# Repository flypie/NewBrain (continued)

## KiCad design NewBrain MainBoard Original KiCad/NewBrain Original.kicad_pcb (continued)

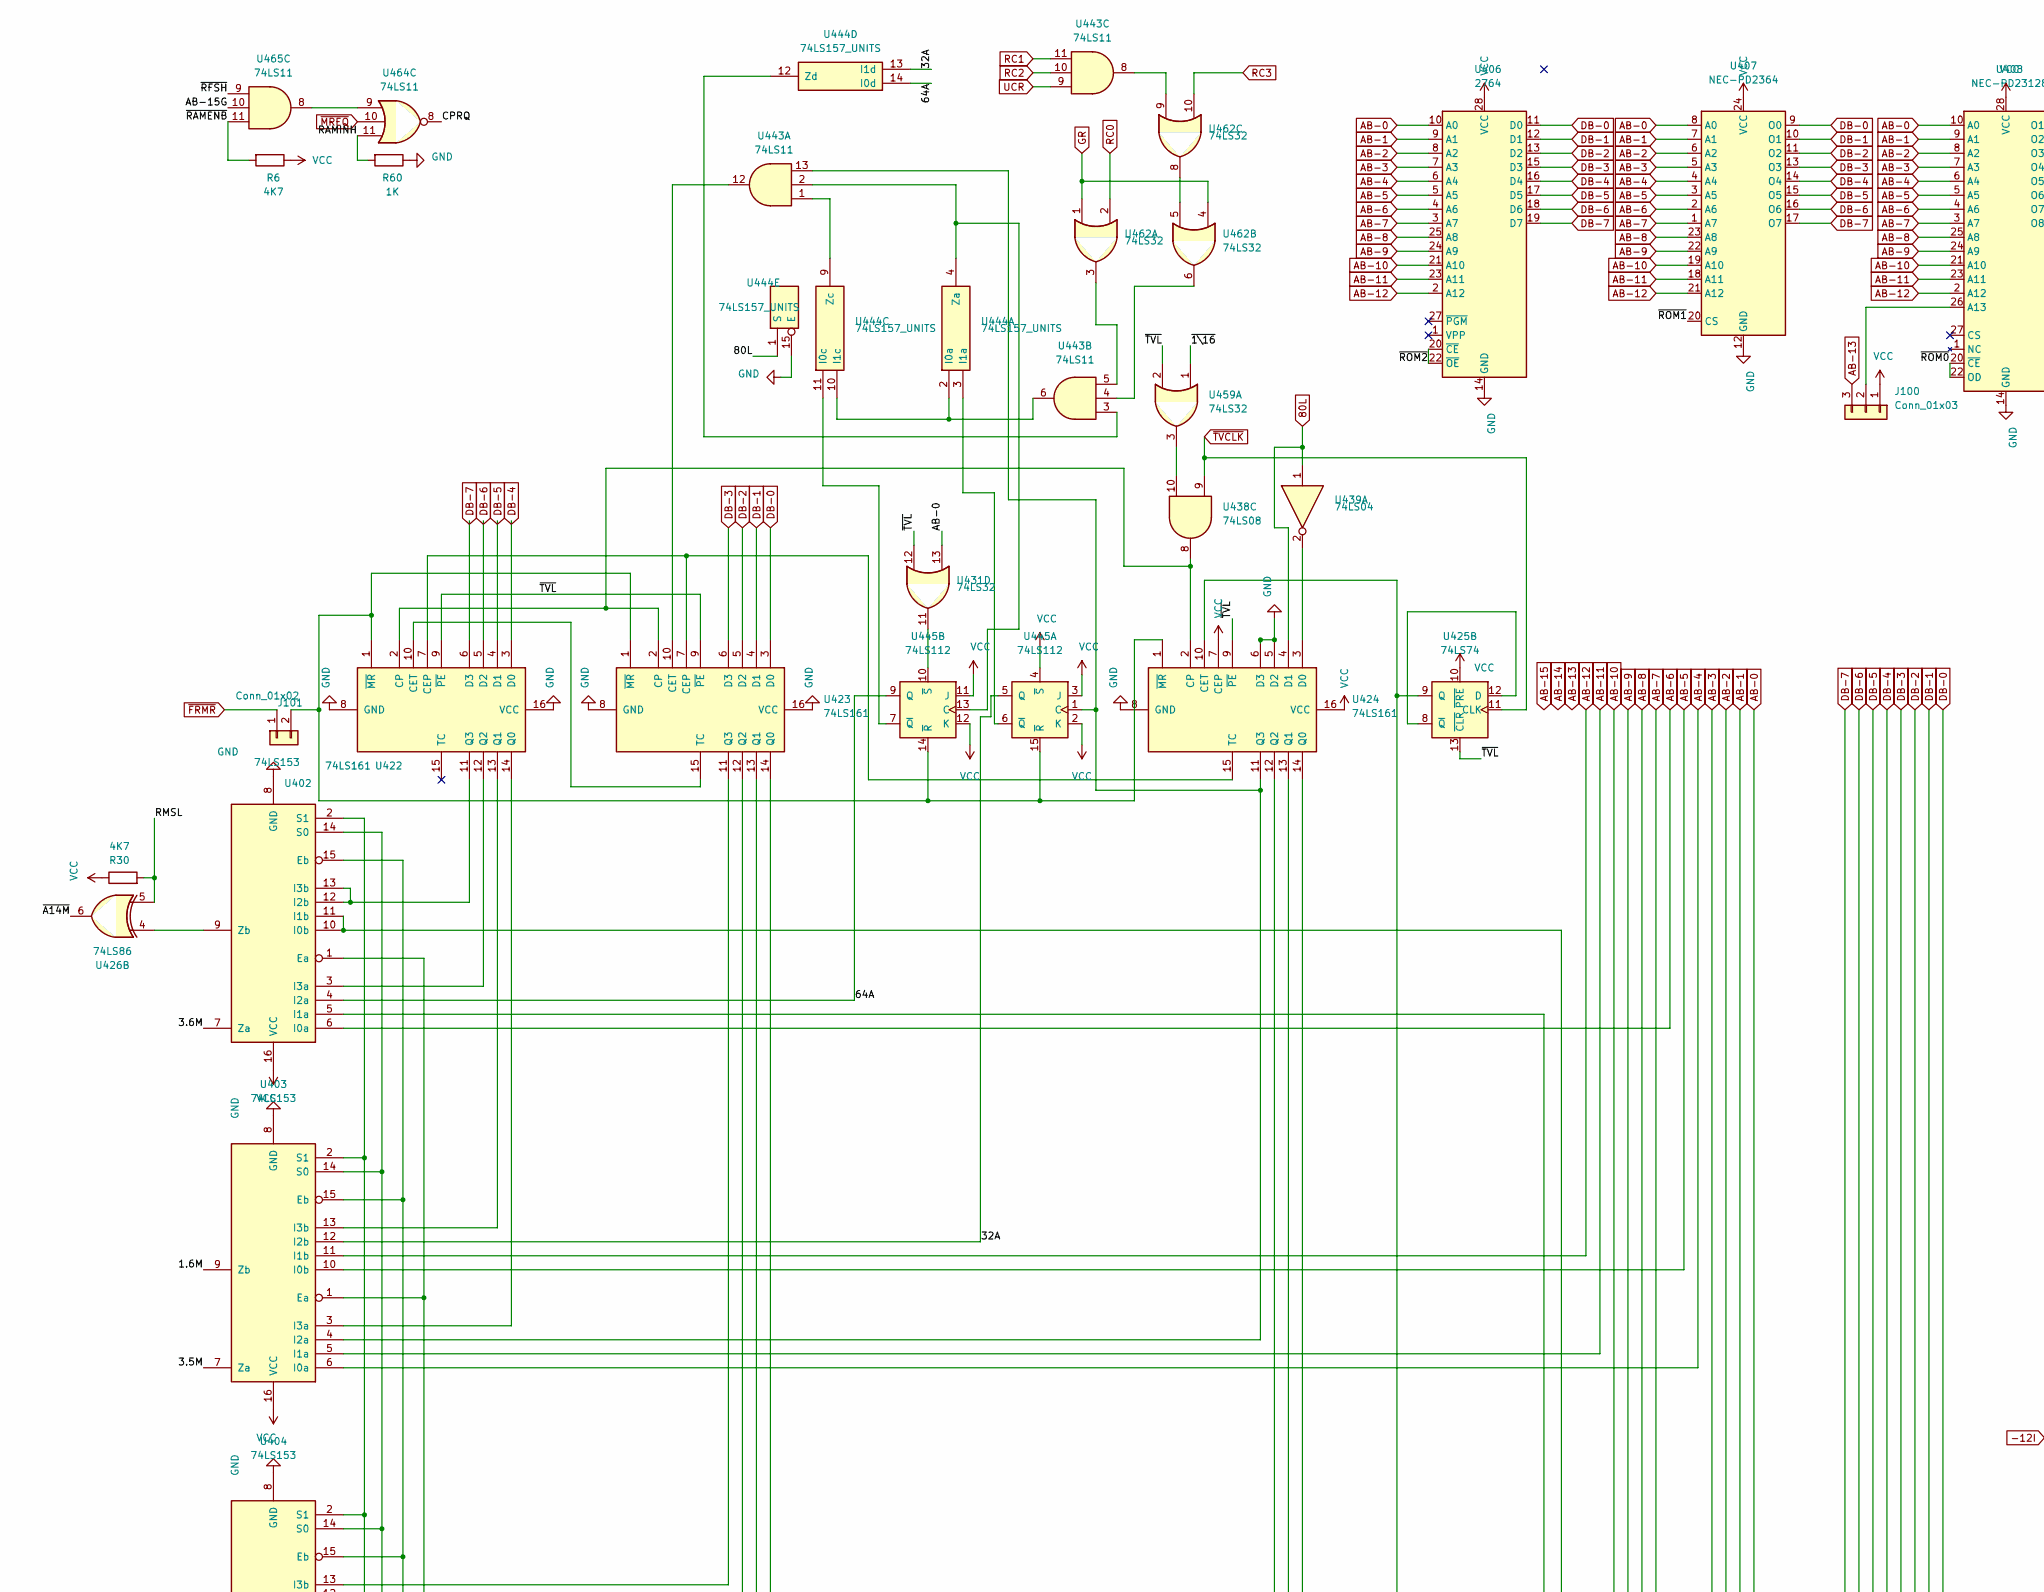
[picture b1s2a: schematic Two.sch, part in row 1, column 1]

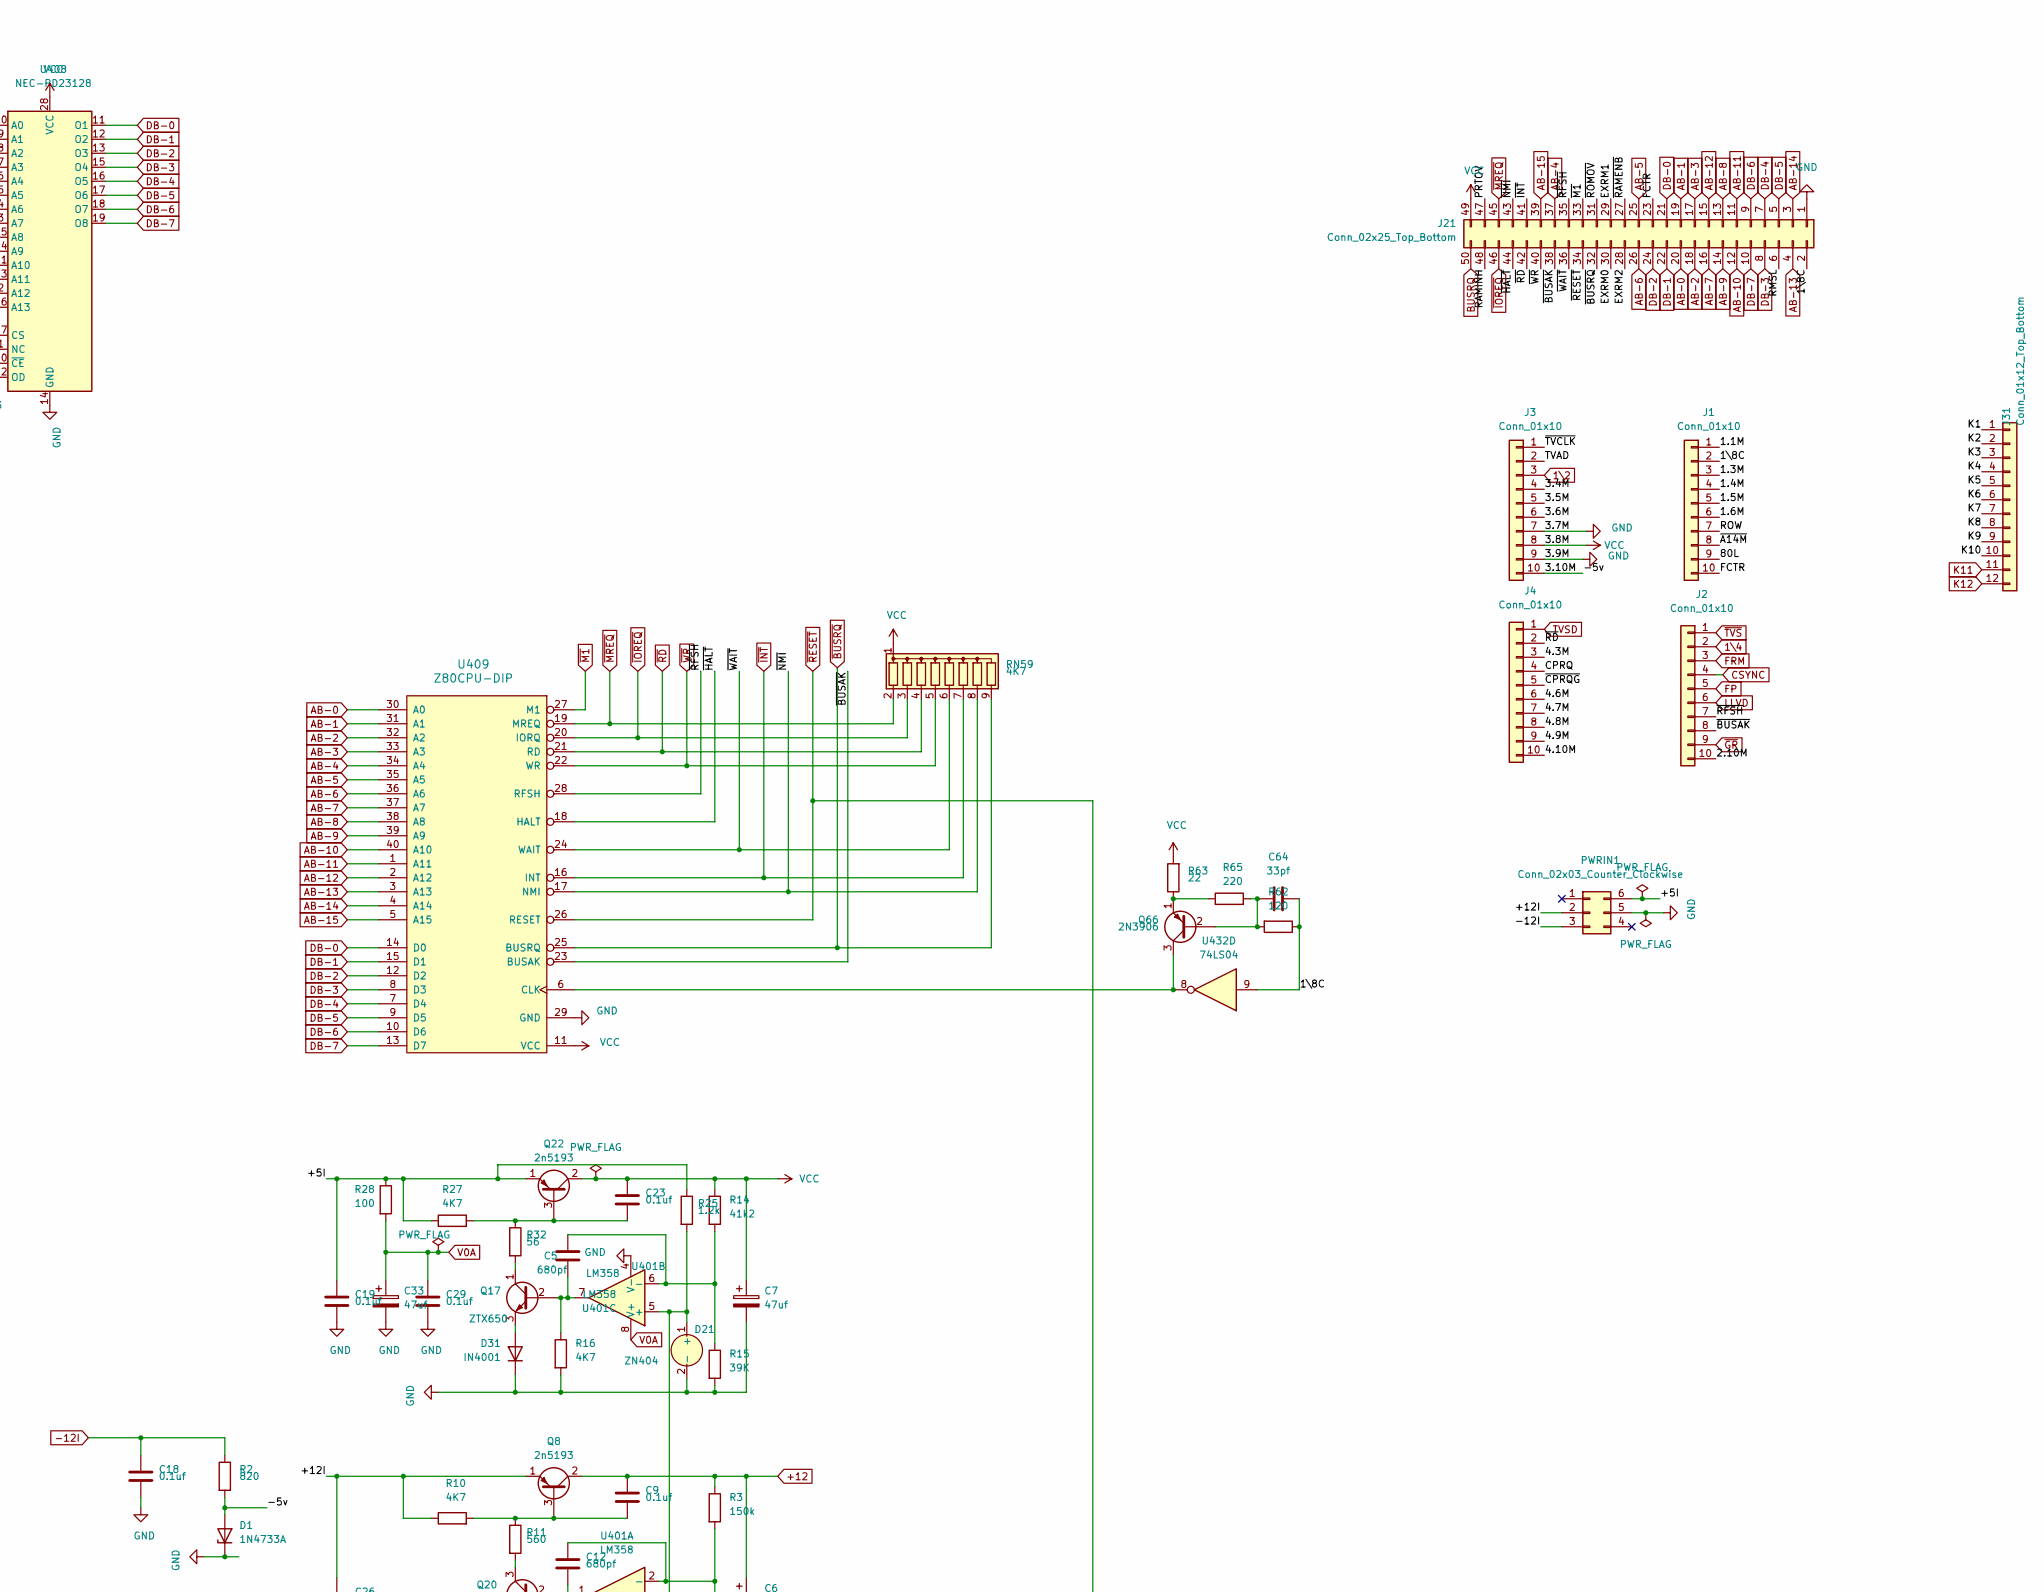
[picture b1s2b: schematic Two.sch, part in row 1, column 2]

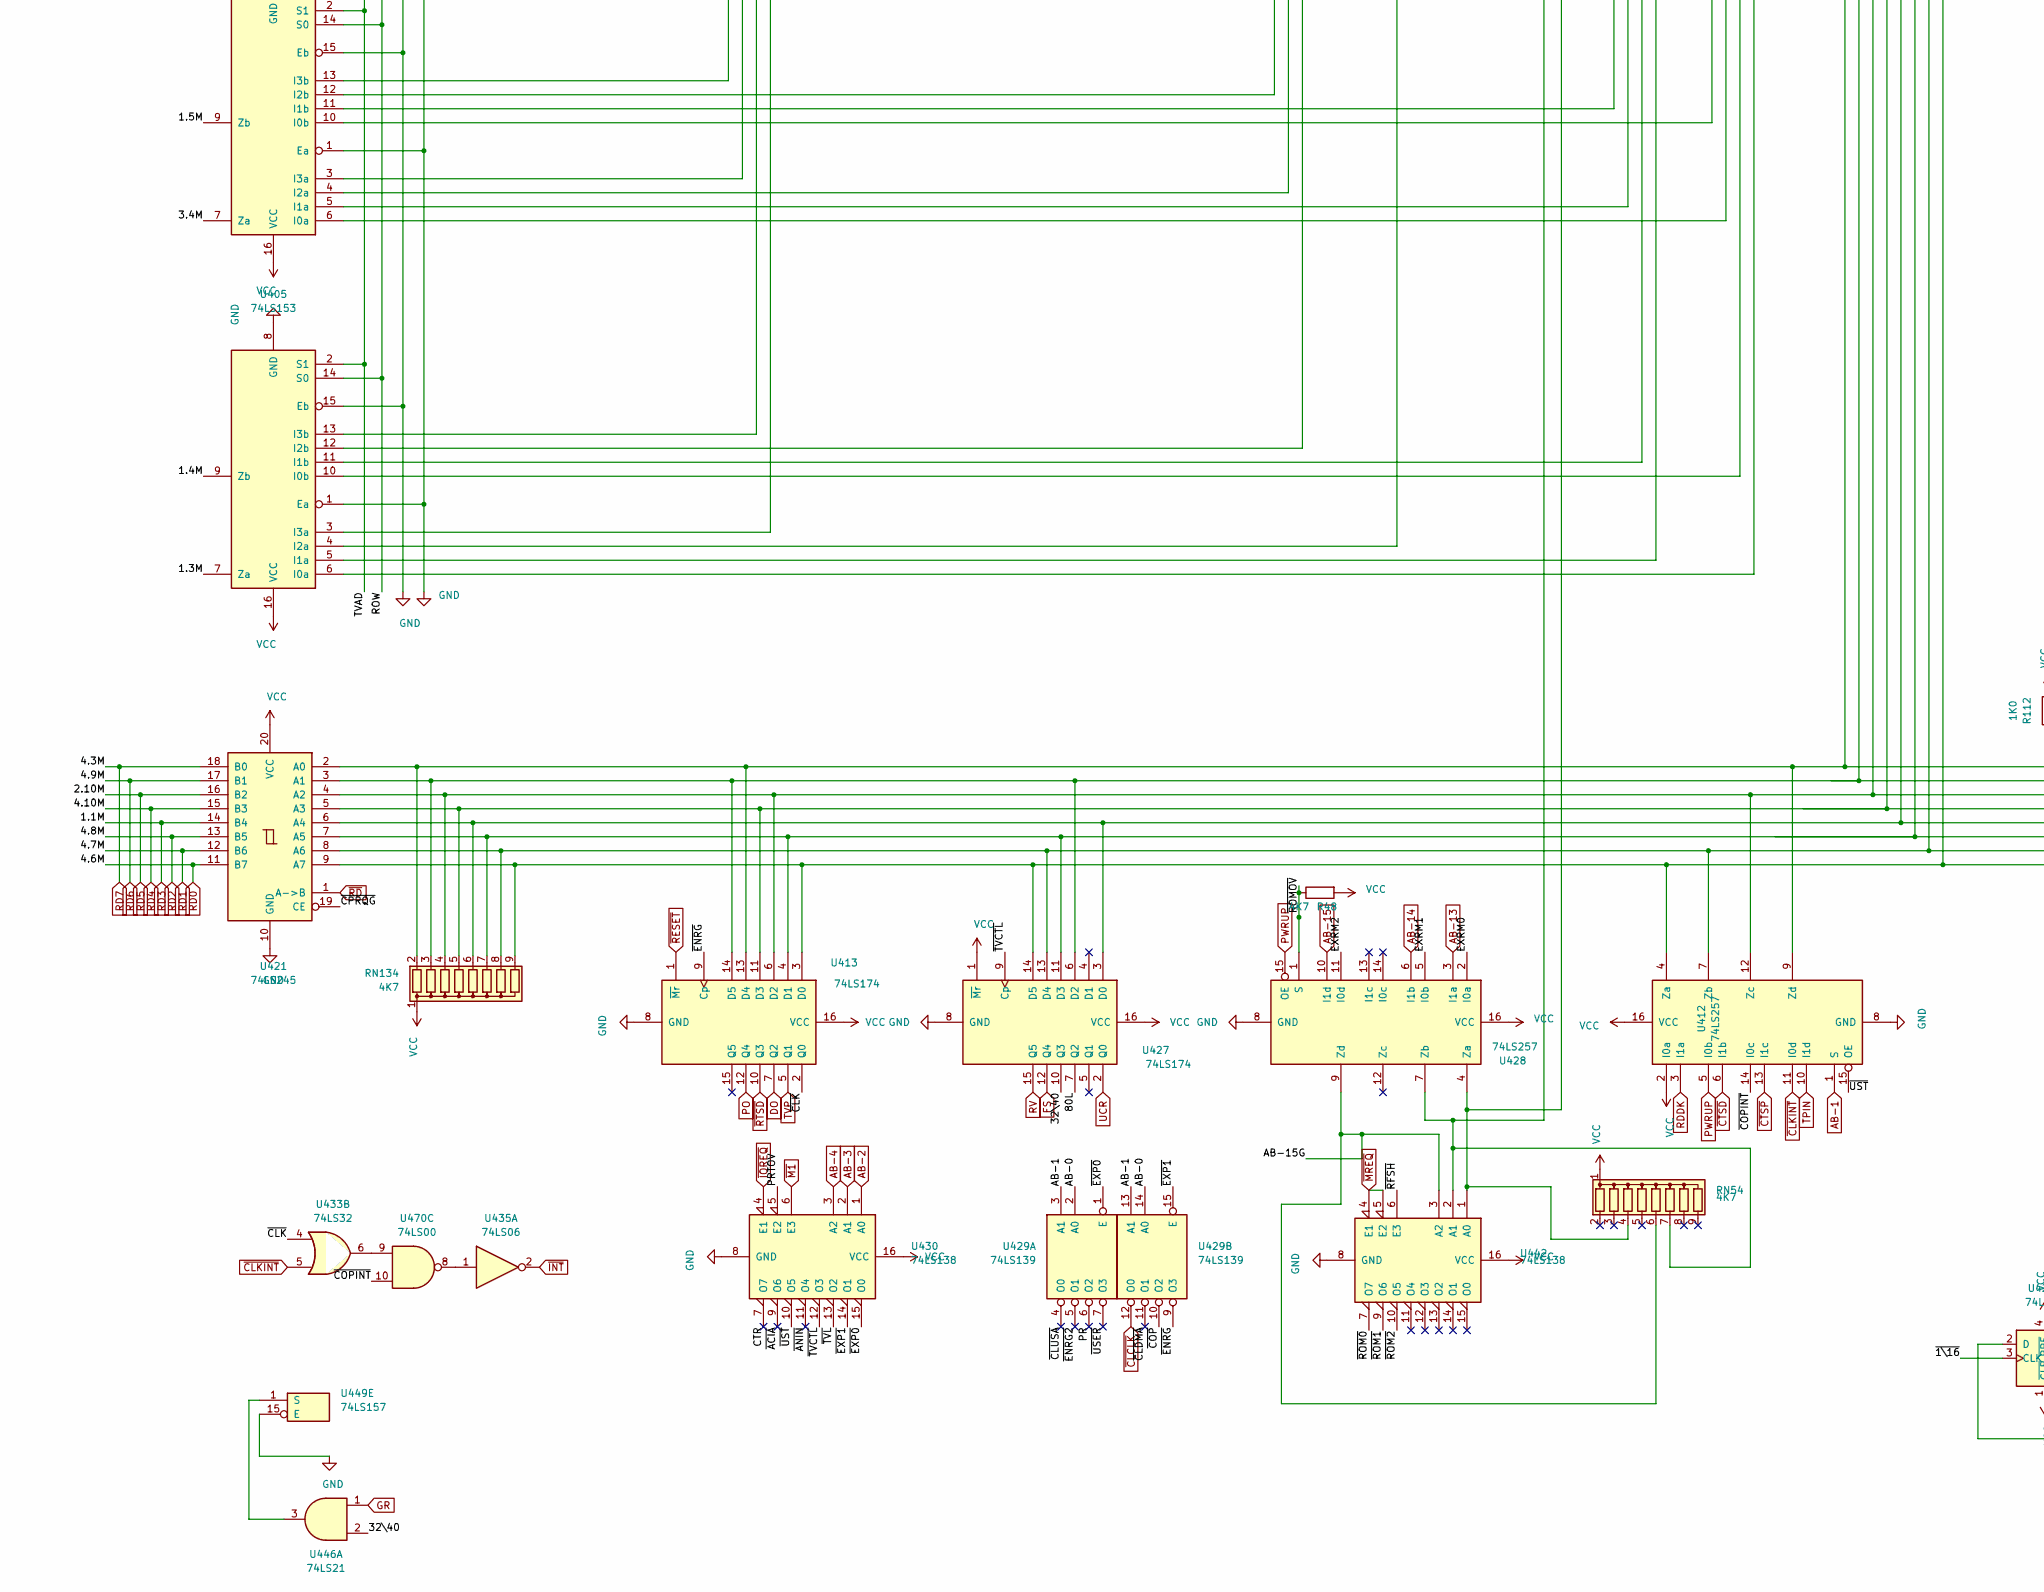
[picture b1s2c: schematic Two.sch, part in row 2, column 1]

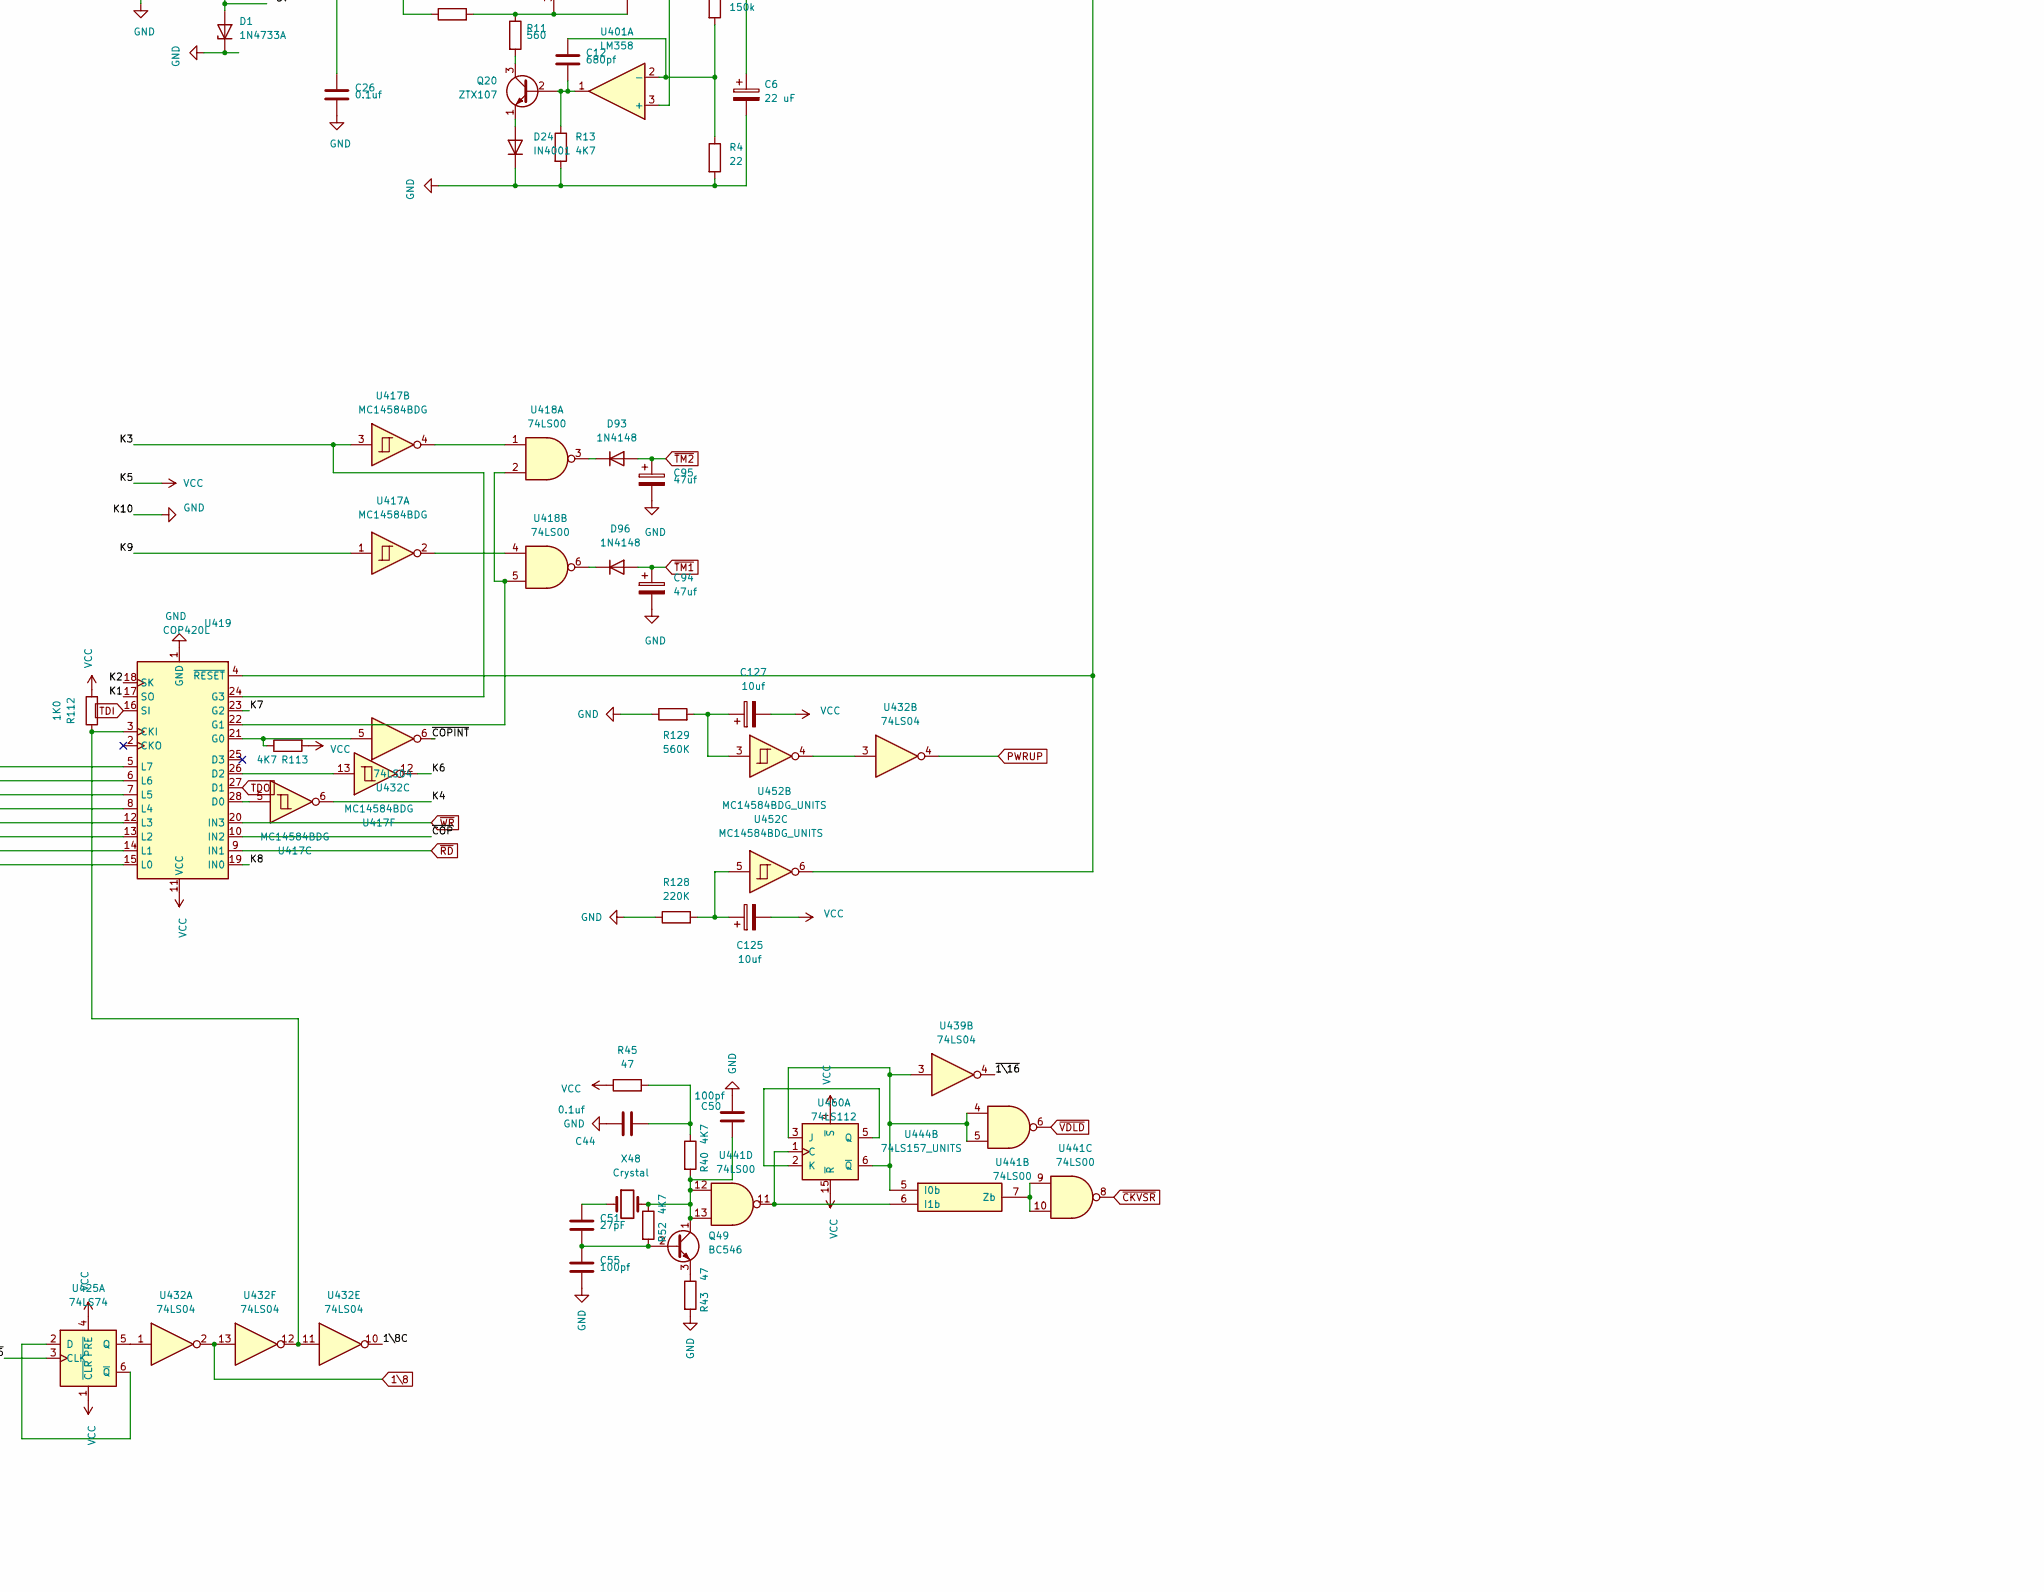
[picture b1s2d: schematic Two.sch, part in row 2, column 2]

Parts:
C5, C12: 680pf; C_Disc_D3.0mm_W1.6mm_P2.50mm
C6: 22 uF; CP_Radial_D4.0mm_P1.50mm
C7, C33, C94, C95: 47uf; CP_Radial_D4.0mm_P1.50mm
C9, C18, C19, C23, C26, C29, C44: 0.1uf; C_Disc_D3.0mm_W1.6mm_P2.50mm
C50, C55: 100pf; C_Disc_D3.0mm_W1.6mm_P2.50mm
C51: 27pF; C_Disc_D3.0mm_W1.6mm_P2.50mm
C64: 33pf; C_Disc_D3.0mm_W1.6mm_P2.50mm
C125, C127: 10uf; CP_Radial_D4.0mm_P1.50mm
D1: 1N4733A; D_DO-34_SOD68_P2.54mm_Vertical_AnodeUp
D21: ZN404; TO-18-2
D24, D31: IN4001; D_DO-34_SOD68_P2.54mm_Vertical_AnodeUp
D93, D96: 1N4148; D_DO-34_SOD68_P2.54mm_Vertical_AnodeUp
J1, J2, J3, J4: Conn_01x10; JST_EH_B10B-EH-A_1x10_P2.50mm_Vertical
J21: Conn_02x25_Top_Bottom; PinHeader_2x25_P2.54mm_Vertical
J31: Conn_01x12_Top_Bottom; JST_EH_B12B-EH-A_1x12_P2.50mm_Vertical
J100: Conn_01x03; PinSocket_1x03_P2.54mm_Vertical
J101: Conn_01x02; PinSocket_1x02_P2.54mm_Vertical
PWRIN1: Conn_02x03_Counter_Clockwise; PinHeader_2x03_P2.54mm_Vertical
Q8, Q22: 2n5193; TO-126-3_Vertical
Q17: ZTX650; TO-92_Inline
Q20: ZTX107; TO-92_Inline
Q49: BC546; TO-92_Inline
Q66: 2N3906; TO-92_Inline
R2: 820; R_Axial_DIN0204_L3.6mm_D1.6mm_P1.90mm_Vertical
R3: 150k; R_Axial_DIN0204_L3.6mm_D1.6mm_P1.90mm_Vertical
R4, R63: 22; R_Axial_DIN0204_L3.6mm_D1.6mm_P1.90mm_Vertical
R6, R10, R13, R16, R27, R30, R40, R48, R52, R113: 4K7; R_Axial_DIN0204_L3.6mm_D1.6mm_P1.90mm_Vertical
R11: 560; R_Axial_DIN0204_L3.6mm_D1.6mm_P1.90mm_Vertical
R14: 41k2; R_Axial_DIN0204_L3.6mm_D1.6mm_P1.90mm_Vertical
R15: 39K; R_Axial_DIN0204_L3.6mm_D1.6mm_P1.90mm_Vertical
R25: 1.2k; R_Axial_DIN0204_L3.6mm_D1.6mm_P1.90mm_Vertical
R28: 100; R_Axial_DIN0204_L3.6mm_D1.6mm_P1.90mm_Vertical
R32: 56; R_Axial_DIN0204_L3.6mm_D1.6mm_P1.90mm_Vertical
R43, R45: 47; R_Axial_DIN0204_L3.6mm_D1.6mm_P1.90mm_Vertical
R60: 1K; R_Axial_DIN0204_L3.6mm_D1.6mm_P1.90mm_Vertical
R62: 120; R_Axial_DIN0204_L3.6mm_D1.6mm_P1.90mm_Vertical
R65: 220; R_Axial_DIN0204_L3.6mm_D1.6mm_P1.90mm_Vertical
R112: 1K0; R_Axial_DIN0204_L3.6mm_D1.6mm_P1.90mm_Vertical
R128: 220K; R_Axial_DIN0204_L3.6mm_D1.6mm_P1.90mm_Vertical
R129: 560K; R_Axial_DIN0204_L3.6mm_D1.6mm_P1.90mm_Vertical
RN54, RN59, RN134: 4K7; R_Array_SIP9
U401: LM358; DIP-8_W7.62mm
U402, U403, U404, U405: 74LS153; DIP-16_W7.62mm
U406: 2764; DIP-28_W15.24mm
U407: NEC-PD2364; DIP-28_W15.24mm
U408: NEC-PD23128; DIP-28_W15.24mm
U409: Z80CPU-DIP; DIP-40_W15.24mm
U412, U428: 74LS257; DIP-16_W7.62mm
U413, U427: 74LS174; DIP-16_W7.62mm
U417: MC14584BDG; DIP-14_W7.62mm
U418, U441, U470: 74LS00; DIP-14_W7.62mm
U419: COP420L; DIP-28_W7.62mm
U421: 74LS245; DIP-20_W7.62mm
U422, U423, U424: 74LS161; DIP-16_W7.62mm
U425: 74LS74; DIP-14_W7.62mm
U426: 74LS86; DIP-14_W7.62mm
U429: 74LS139; DIP-16_W7.62mm
U430, U442: 74LS138; DIP-16_W7.62mm
U431, U433, U459, U462: 74LS32; DIP-14_W7.62mm
U432, U439: 74LS04; DIP-14_W7.62mm
U435: 74LS06; DIP-14_W7.62mm
U438: 74LS08; DIP-14_W7.62mm
U443, U464, U465: 74LS11; DIP-14_W7.62mm
U444: 74LS157_UNITS; DIP-16_W7.62mm
U445, U460: 74LS112; DIP-16_W7.62mm
U446: 74LS21; DIP-14_W7.62mm
U449: 74LS157; DIP-16_W7.62mm
U452: MC14584BDG_UNITS; DIP-14_W7.62mm
X48: Crystal; Crystal_HC52-6mm_Vertical

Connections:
1\2: J3.3; also elsewhere on the board
1\4: J2.2; also elsewhere on the board
1\8: U432.2, U432.13; also elsewhere on the board
80L: J1.9, U424.4 (D1), U427.7 (Q2), U439.1, U444.1 (S); also elsewhere on the board
+12: C6.1, C9.2, Q8.2 (C), R3.1; also elsewhere on the board
-12I: C18.2, PWRIN1.3, R2.1; also elsewhere on the board
/TWO/1.3M: J1.3, U405.7 (Za)
/TWO/1.4M: J1.4, U405.9 (Zb)
/TWO/1.5M: J1.5, U404.9 (Zb)
/TWO/1.6M: J1.6, U403.9 (Zb)
/TWO/1\8C: C64.1, J1.2, J21.2, R62.1, U432.9, U432.10
/TWO/3.4M: J3.4, U404.7 (Za)
/TWO/3.5M: J3.5, U403.7 (Za)
/TWO/3.6M: J3.6, U402.7 (Za)
/TWO/32A: U403.12 (I2b), U444.13 (I1d), U445.5 (Q)
/TWO/32\40: U427.10 (Q3), U446.2
/TWO/64A: U402.4 (I2a), U444.14 (I0d), U445.9 (Q)
/TWO/+5I: C19.2, PWRIN1.6, Q22.1 (E), R25.1, R27.1, R28.1
/TWO/+12I: C26.2, PWRIN1.2, Q8.1 (E), R10.1
/TWO/-5v: D1.2 (A), J3.10, R2.2
/TWO/AB-15G: RN54.6 (R5), U428.9 (Zd), U442.3 (A2), U465.10
/TWO/CPRQ: J4.4, U464.8
/TWO/CTR: U430.7 (O7)
/TWO/EXRM0: J21.30, U428.2 (I0a)
/TWO/EXRM1: J21.29, U428.5 (I0b)
/TWO/EXRM2: J21.28, U428.11 (I0d)
/TWO/FCTR: J1.10, J21.23
/TWO/K1: J31.1, U419.17 (SO)
/TWO/K2: J31.2, U419.18 (SK)
/TWO/K3: J31.3, U417.3, U419.24 (G3)
/TWO/K4: J31.4, U417.6
/TWO/K6: J31.6, U417.12
/TWO/K7: J31.7, U419.23 (G2)
/TWO/K8: J31.8, U419.19 (IN0)
/TWO/K9: J31.9, U417.1
/TWO/PR: U429.6 (O2)
/TWO/PRTOV: J21.47, U430.5 (E2)
/TWO/RAMINH: J21.48, R60.2, U464.11
/TWO/RMSL: J21.6, R30.2, U426.5
/TWO/ROW: J1.7, U402.14 (S0), U403.14 (S0), U404.14 (S0), U405.14 (S0)
/TWO/TVAD: J3.2, U402.2 (S1), U403.2 (S1), U404.2 (S1), U405.2 (S1)
/TWO/~1\16: U425.3 (CLK), U439.4, U459.1
/TWO/~A14M: J1.8, U426.6
/TWO/~ACIA: U430.9 (O6)
/TWO/~ANIN: U430.11 (O4)
/TWO/~BUSAK: J2.8, J21.38, U409.23 (BUSAK)
/TWO/~CLDMA: U429.11 (O1)
/TWO/~CLK: U413.2 (Q0), U433.4
/TWO/~CLUSA: U429.4 (O0)
/TWO/~COP: U419.10 (IN2), U429.10 (O2)
/TWO/~COPINT: U412.14 (I0c), U432.6, U470.10
/TWO/~CPRQG: J4.5, U421.19 (CE)
/TWO/~ENRG: U413.9 (Cp), U429.9 (O3)
/TWO/~ENRG2: U429.5 (O1)
/TWO/~EXP0: U429.1 (E), U430.15 (O0)
/TWO/~EXP1: U429.15 (E), U430.14 (O1)
/TWO/~HALT: J21.44, U409.18 (HALT)
/TWO/~NMI: J21.43, RN59.8 (R7), U409.17 (NMI)
/TWO/~RAMENB: J21.27, R6.2, U465.11
/TWO/~RFSH: J2.7, J21.35, U409.28 (RFSH), U442.6 (E3), U465.9
/TWO/~ROM0: U408.20 (~CE), U408.22 (OD), U442.7 (O7)
/TWO/~ROM1: U407.20 (CS), U442.9 (O6)
/TWO/~ROM2: U406.20 (~CE), U406.22 (~OE), U442.10 (O5)
/TWO/~ROMOV: J21.31, R48.1, U428.1 (S)
/TWO/~TVCTL: U427.9 (Cp), U430.12 (O3)
/TWO/~TVL: U422.9 (~PE), U423.9 (~PE), U424.9 (~PE), U425.13 (~CLR), U430.13 (O2), U431.12, U459.2
/TWO/~USER: U429.7 (O3)
/TWO/~UST: U412.15 (OE), U430.10 (O5)
/TWO/~WAIT: J21.36, RN59.6 (R5), U409.24 (WAIT)
AB-0: J21.20, U405.6 (I0a), U406.10 (A0), U407.8 (A0), U408.10 (A0), U409.30 (A0), U429.2 (A0), U429.14 (A0), U431.13
AB-1: J21.19, U405.10 (I0b), U406.9 (A1), U407.7 (A1), U408.9 (A1), U409.31 (A1), U412.1 (S), U429.3 (A1), U429.13 (A1)
AB-2: J21.18, U404.6 (I0a), U406.8 (A2), U407.6 (A2), U408.8 (A2), U409.32 (A2), U430.1 (A0)
AB-3: J21.17, U404.10 (I0b), U406.7 (A3), U407.5 (A3), U408.7 (A3), U409.33 (A3), U430.2 (A1)
AB-4: J21.37, U403.6 (I0a), U406.6 (A4), U407.4 (A4), U408.6 (A4), U409.34 (A4), U430.3 (A2)
AB-5: J21.25, U403.10 (I0b), U406.5 (A5), U407.3 (A5), U408.5 (A5), U409.35 (A5)
AB-6: J21.26, U402.6 (I0a), U406.4 (A6), U407.2 (A6), U408.4 (A6), U409.36 (A6)
AB-7: J21.16, U405.5 (I1a), U406.3 (A7), U407.1 (A7), U408.3 (A7), U409.37 (A7)
AB-8: J21.13, U405.11 (I1b), U406.25 (A8), U407.23 (A8), U408.25 (A8), U409.38 (A8)
AB-9: J21.14, U404.5 (I1a), U406.24 (A9), U407.22 (A9), U408.24 (A9), U409.39 (A9)
AB-10: J21.12, U404.11 (I1b), U406.21 (A10), U407.19 (A10), U408.21 (A10), U409.40 (A10)
AB-11: J21.11, U403.5 (I1a), U406.23 (A11), U407.18 (A11), U408.23 (A11), U409.1 (A11)
AB-12: J21.15, U403.11 (I1b), U406.2 (A12), U407.21 (A12), U408.2 (A12), U409.2 (A12)
AB-13: J21.4, J100.3, U409.3 (A13), U428.3 (I1a)
AB-14: J21.3, U409.4 (A14), U428.6 (I1b)
AB-15: J21.39, U409.5 (A15), U428.10 (I1d)
BUSRQ: J21.50; also elsewhere on the board
CSYNC: J2.4; also elsewhere on the board
DB-0: J21.21, RN134.9 (R8), U406.11 (D0), U407.9 (O0), U408.11 (O1), U409.14 (D0), U412.4 (Za), U413.3 (D0), U419.15 (L0), U421.9 (A7), U423.3 (D0), U427.14 (D5)
DB-1: J21.22, RN134.8 (R7), U406.12 (D1), U407.10 (O1), U408.12 (O2), U409.15 (D1), U412.7 (Zb), U419.14 (L1), U421.8 (A6), U423.4 (D1), U427.13 (D4)
DB-2: J21.24, RN134.7 (R6), U406.13 (D2), U407.11 (O2), U408.13 (O3), U409.12 (D2), U413.4 (D1), U419.13 (L2), U421.7 (A5), U423.5 (D2), U427.11 (D3)
DB-3: J21.8, RN134.6 (R5), U406.15 (D3), U407.13 (O3), U408.15 (O4), U409.8 (D3), U419.12 (L3), U421.6 (A4), U423.6 (D3), U427.3 (D0)
DB-4: J21.7, RN134.5 (R4), U406.16 (D4), U407.14 (O4), U408.16 (O5), U409.7 (D4), U413.11 (D3), U419.8 (L4), U421.5 (A3), U422.3 (D0)
DB-5: J21.5, RN134.4 (R3), U406.17 (D5), U407.15 (O5), U408.17 (O6), U409.9 (D5), U412.12 (Zc), U413.6 (D2), U419.7 (L5), U421.4 (A2), U422.4 (D1)
DB-6: J21.9, RN134.3 (R2), U406.18 (D6), U407.16 (O6), U408.18 (O7), U409.10 (D6), U413.14 (D5), U419.6 (L6), U421.3 (A1), U422.5 (D2), U427.6 (D2)
DB-7: J21.10, RN134.2 (R1), U406.19 (D7), U407.17 (O7), U408.19 (O8), U409.13 (D7), U412.9 (Zd), U413.13 (D4), U419.5 (L7), U421.2 (A0), U422.6 (D3)
DO: U413.7 (Q2); also elsewhere on the board
FP: J2.5; also elsewhere on the board
FRM: J2.3; also elsewhere on the board
FS: U427.12 (Q4); also elsewhere on the board
GR: U446.1, U462.1, U462.4; also elsewhere on the board
K11: J31.11; also elsewhere on the board
K12: C6.2, C7.2, C18.1, C19.1, C26.1, C29.1, C33.2, C44.1, C50.1, C55.1, C94.2, C95.2, D1.1 (K), D21.2 (-), D24.1 (K), D31.1 (K), J3.7, J3.9, J21.1, J31.10, J31.12, PWRIN1.5, R4.2, R13.2, R15.2, R16.2, R43.2, R60.1, R128.1, R129.1, U401.4 (V-), U402.1 (Ea), U402.8 (GND), U402.15 (Eb), U403.1 (Ea), U403.8 (GND), U403.15 (Eb), U404.1 (Ea), U404.8 (GND), U404.15 (Eb), U405.1 (Ea), U405.8 (GND), U405.15 (Eb), U406.14 (GND), U407.12 (GND), U408.14 (GND), U409.29 (GND), U412.8 (GND), U413.8 (GND), U419.1 (GND), U421.10 (GND), U422.8 (GND), U422.16 (VCC), U423.8 (GND), U423.16 (VCC), U424.5 (D2), U424.6 (D3), U424.8 (GND), U427.8 (GND), U428.8 (GND), U430.8 (GND), U442.8 (GND), U444.15 (E), U449.15 (E); also elsewhere on the board
LLVD: J2.6; also elsewhere on the board
unnamed: C5.1, Q17.2 (B), R16.1, U401.7
unnamed: C5.2, R14.2, R15.1, U401.6 (-)
unnamed: C9.1, Q8.3 (B), R10.2, R11.1
unnamed: C12.1, Q20.2 (B), R13.1, U401.1
unnamed: C12.2, R3.2, R4.1, U401.2 (-)
unnamed: C23.1, Q22.3 (B), R27.2, R32.1
unnamed: C44.2, R40.1, R45.2
unnamed: C50.2, Q49.1 (C), R40.2, R52.1, U441.12, U441.13, X48.2
unnamed: C51.1, C55.2, Q49.2 (B), R52.2
unnamed: C51.2, X48.1
unnamed: C64.2, Q66.2 (B), R62.2, R65.2
unnamed: C125.1, R128.2, U452.5
unnamed: C127.1, R129.2, U452.3
unnamed: D21.1 (+), R25.2, U401.3 (+), U401.5 (+)
unnamed: D24.2 (A), Q20.1 (E)
unnamed: D31.2 (A), Q17.3 (E)
unnamed: D93.1 (K), U418.3
unnamed: D96.1 (K), U418.6
unnamed: J100.2, U408.26 (A13)
unnamed: J101.2, U422.1 (~MR), U423.1 (~MR), U424.1 (~MR), U445.14 (~R), U445.15 (~R)
unnamed: Q17.1 (C), R32.2
unnamed: Q20.3 (C), R11.2
unnamed: Q49.3 (E), R43.1
unnamed: Q66.1 (E), R63.1, R65.1
unnamed: Q66.3 (C), U409.6 (CLK), U432.8
unnamed: R112.1, U419.3 (CKI), U432.11, U432.12
unnamed: R113.1, U419.21 (G0), U432.5
unnamed: RN54.4 (R3), U402.10 (I0b), U402.11 (I1b), U428.4 (Za), U442.1 (A0)
unnamed: RN54.7 (R6), U402.5 (I1a), U428.7 (Zb), U442.2 (A1)
unnamed: U402.3 (I3a), U422.12 (Q2)
unnamed: U402.9 (Zb), U426.4
unnamed: U402.12 (I2b), U402.13 (I3b), U422.11 (Q3)
unnamed: U403.3 (I3a), U422.14 (Q0)
unnamed: U403.4 (I2a), U424.11 (Q3), U443.13, U445.1 (C)
unnamed: U403.13 (I3b), U422.13 (Q1)
unnamed: U404.3 (I3a), U423.12 (Q2)
unnamed: U404.4 (I2a), U424.13 (Q1)
unnamed: U404.12 (I2b), U424.12 (Q2)
unnamed: U404.13 (I3b), U423.11 (Q3)
unnamed: U405.3 (I3a), U423.14 (Q0)
unnamed: U405.4 (I2a), U424.10 (CET), U425.9 (Q)
unnamed: U405.12 (I2b), U424.14 (Q0)
unnamed: U405.13 (I3b), U423.13 (Q1)
unnamed: U417.2, U418.4
unnamed: U417.4, U418.1
unnamed: U417.5, U419.28 (D0)
unnamed: U417.13, U419.26 (D2)
unnamed: U418.2, U418.5, U419.22 (G1)
unnamed: U422.2 (CP), U423.2 (CP), U424.2 (CP), U438.8
unnamed: U422.7 (CEP), U423.7 (CEP), U424.15 (TC)
unnamed: U422.10 (CET), U423.15 (TC)
unnamed: U423.10 (CET), U443.12
unnamed: U424.3 (D0), U439.2
unnamed: U425.2 (D), U425.6 (~Q)
unnamed: U425.5 (Q), U432.1
unnamed: U425.8 (~Q), U425.12 (D)
unnamed: U431.11, U445.10 (~S)
unnamed: U432.3, U452.4
unnamed: U433.6, U470.9
unnamed: U435.1, U470.8
unnamed: U438.10, U459.3
unnamed: U439.3, U441.4, U441.5, U444.5 (I0b), U460.3 (J), U460.6 (~Q)
unnamed: U441.9, U441.10, U444.7 (Zb)
unnamed: U441.11, U444.6 (I1b), U460.1 (C)
unnamed: U443.1, U444.9 (Zc)
unnamed: U443.2, U444.4 (Za), U445.13 (C)
unnamed: U443.3, U444.12 (Zd)
unnamed: U443.4, U462.6
unnamed: U443.5, U462.3
unnamed: U443.6, U444.2 (I0a), U444.10 (I1c)
unnamed: U443.8, U462.9
unnamed: U444.3 (I1a), U445.6 (~Q)
unnamed: U444.11 (I0c), U445.7 (~Q)
unnamed: U446.3, U449.1 (S)
unnamed: U460.2 (K), U460.5 (Q)
unnamed: U462.5, U462.8
unnamed: U464.9, U465.8
PO: U413.12 (Q4); also elsewhere on the board
PWRUP: U412.5 (I0b), U428.15 (OE), U432.4
RC0: U462.2; also elsewhere on the board
RC1: U443.11; also elsewhere on the board
RC2: U443.10; also elsewhere on the board
RC3: U462.10; also elsewhere on the board
RD0: J4.6, U421.11 (B7); also elsewhere on the board
RD1: J4.7, U421.12 (B6); also elsewhere on the board
RD2: J4.8, U421.13 (B5); also elsewhere on the board
RD3: J1.1, U421.14 (B4); also elsewhere on the board
RD4: J4.10, U421.15 (B3); also elsewhere on the board
RD5: J2.10, U421.16 (B2); also elsewhere on the board
RD6: J4.9, U421.17 (B1); also elsewhere on the board
RD7: J4.3, U421.18 (B0); also elsewhere on the board
RDDK: U412.3 (I1a); also elsewhere on the board
RV: U427.15 (Q5); also elsewhere on the board
TDI: U419.16 (SI); also elsewhere on the board
TDO: U419.27 (D1); also elsewhere on the board
TPIN: U412.10 (I1d); also elsewhere on the board
TVP: U413.5 (Q1); also elsewhere on the board
TVSD: J4.1; also elsewhere on the board
UCR: U427.2 (Q0), U443.9; also elsewhere on the board
V0A: C29.2, C33.1, R28.2, U401.8 (V+); also elsewhere on the board
VCC: C7.1, C23.2, C125.2, C127.2, J3.8, J21.49, J31.5, J100.1, Q22.2 (C), R6.1, R14.1, R30.1, R45.1, R48.2, R63.2, R112.2, R113.2, RN54.1 (common), RN59.1 (common), RN134.1 (common), U402.16 (VCC), U403.16 (VCC), U404.16 (VCC), U405.16 (VCC), U406.28 (VCC), U407.24 (VCC), U408.28 (VCC), U409.11 (VCC), U412.2 (I0a), U412.16 (VCC), U413.16 (VCC), U419.11 (VCC), U421.20 (VCC), U424.7 (CEP), U424.16 (VCC), U425.1 (~CLR), U425.4 (~PRE), U425.10 (~PRE), U427.1 (~Mr), U427.16 (VCC), U428.16 (VCC), U430.16 (VCC), U442.16 (VCC), U445.2 (K), U445.3 (J), U445.4 (~S), U445.11 (J), U445.12 (K), U460.4 (~S), U460.15 (~R); also elsewhere on the board
~BUSRQ: J21.32, RN59.9 (R8), U409.25 (BUSRQ); also elsewhere on the board
~CKVSR: U441.8; also elsewhere on the board
~CLCLK: U429.12 (O0); also elsewhere on the board
~CLKINT: U412.11 (I0d), U433.5; also elsewhere on the board
~CTSD: U412.6 (I1b); also elsewhere on the board
~CTSP: U412.13 (I1c); also elsewhere on the board
~FRMR: J101.1; also elsewhere on the board
~GR: J2.9; also elsewhere on the board
~INT: J21.41, RN59.7 (R6), U409.16 (INT), U435.2
~IOREQ: J21.46, RN59.3 (R2), U409.20 (IORQ), U430.4 (E1)
~M1: J21.33, U409.27 (M1), U430.6 (E3)
~MREQ: J21.45, RN59.2 (R1), U409.19 (MREQ), U442.4 (E1), U442.5 (E2), U464.10
~RD: J4.2, J21.42, RN59.4 (R3), U409.21 (RD), U419.9 (IN1), U421.1 (A->B)
~RESET: J21.34, U409.26 (RESET), U413.1 (~Mr), U419.4 (~RESET), U452.6
~RTSD: U413.10 (Q3); also elsewhere on the board
~TM1: C94.1, D96.2 (A); also elsewhere on the board
~TM2: C95.1, D93.2 (A); also elsewhere on the board
~TVCLK: J3.1, U425.11 (CLK), U438.9; also elsewhere on the board
~TVS: J2.1; also elsewhere on the board
~VDLD: U441.6; also elsewhere on the board
~WR: J21.40, RN59.5 (R4), U409.22 (WR), U419.20 (IN3)
